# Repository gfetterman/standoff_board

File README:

# Standoff board

This board provides an interface between an [analog headstage](https://github.com/gfetterman/analog_headstage) and Intan amplifiers. It is intended for use in small-animal electrophysiology.

The board currently supports 7 channels, matching the analog headstage linked above.

It also provides the option of stepping down a signal to match the amplifiers' input range. The current default is a 62x attenuation. To pass a signal straight through, without attenuation, replace the appropriate resistor (one of R1-R7) with a jumper cable or zero-Ohm resistor, and remove the corresponding grounding resistor (one of R8-R14).

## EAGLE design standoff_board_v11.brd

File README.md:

# Standoff board

This board provides an interface between an [analog headstage](https://github.com/gfetterman/analog_headstage) and Intan amplifiers. It is intended for use in small-animal electrophysiology.

The board currently supports 7 channels, matching the analog headstage linked above.

It also provides the option of stepping down a signal to match the amplifiers' input range. The current schematic provides a 62x attenuation, but any resistor pair may be substituted in the voltage dividers during construction. To pass a signal straight through, without attenuation, replace the appropriate resistor (one of R1-R7) with a jumper cable or zero-Ohm resistor, and remove the corresponding grounding resistor (one of R8-R14).

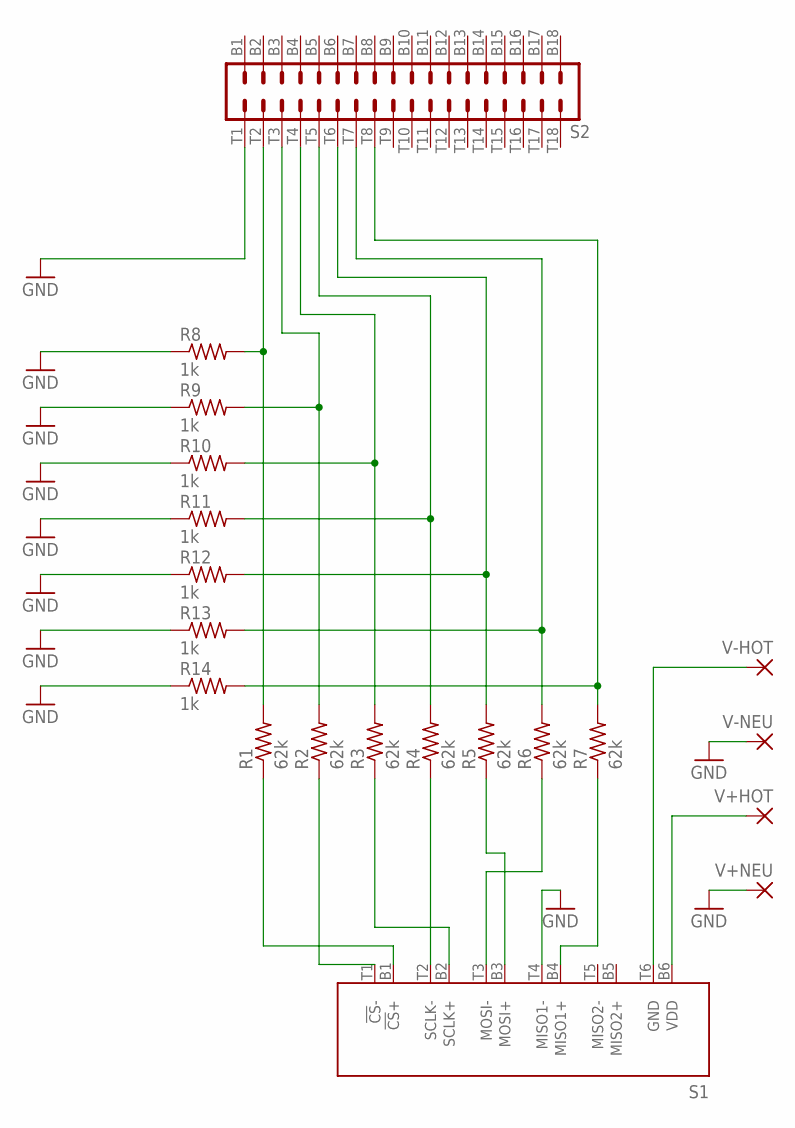
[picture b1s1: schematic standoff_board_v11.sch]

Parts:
R1, R2, R3, R4, R5, R6, R7: 62k; 0204/7
R8, R9, R10, R11, R12, R13, R14: 1k; 0204/7
S1: RHD2000-CABLE-DAQ-SIDE; OMNETICS_PZN-12-AA
S2: OMNETICS_A79025
V+HOT: 2,54/1,1
V+NEU: 2,54/1,1
V-HOT: 2,54/1,1
V-NEU: 2,54/1,1

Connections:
A1POST: R1.2, R8.2, S2.T2
A1PRE: R1.1, S1.B1 (!CS!+)
A2POST: R2.2, R9.2, S2.T3
A2PRE: R2.1, S1.T1 (!CS!-)
A3POST: R3.2, R10.2, S2.T4
A3PRE: R3.1, S1.B2 (SCLK+)
A4POST: R4.2, R11.2, S2.T5
A4PRE: R4.1, S1.T2 (SCLK-)
A5POST: R5.2, R12.2, S2.T6
A5PRE: R5.1, S1.B3 (MOSI+)
A6POST: R6.2, R13.2, S2.T7
A6PRE: R6.1, S1.T3 (MOSI-)
A7POST: R7.2, R14.2, S2.T8
A7PRE: R7.1, S1.B4 (MISO1+)
GND: R8.1, R9.1, R10.1, R11.1, R12.1, R13.1, R14.1, S1.T4 (MISO1-), S2.T1, V+NEU.1, V-NEU.1
V+HOT: S1.B6 (VDD), V+HOT.1
V-HOT: S1.T6 (GND), V-HOT.1

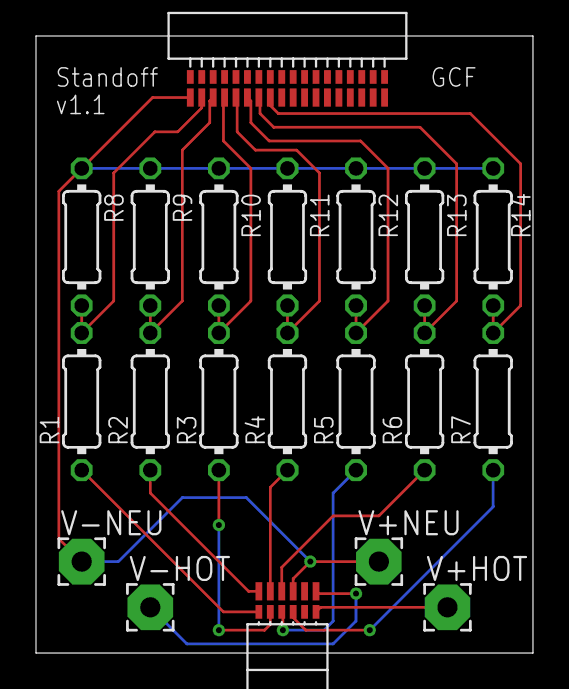
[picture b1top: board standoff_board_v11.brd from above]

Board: 2 copper layers, 27.6 x 34.3 mm, 20 parts (0 on the bottom side), 17 nets.

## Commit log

2017-03-09 Populate
2017-03-09 Reroute output traces symmetrically
2017-03-09 Add README
2017-03-09 Add bill of materials
2017-03-09 Rename README
2017-03-09 Fix typo
2017-03-09 Fix NPD-36-AA part number
2017-03-09 Clarify wording
